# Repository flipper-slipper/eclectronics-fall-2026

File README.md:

# eclectronics-fall-2026
coursework for the eclectronics class at olin collge for the fall 2026 semester. includes pcb design, project reports, circuit simulations.

## Projects
- [Miniproject 1: USB-powered 1 Hz LED flasher PCB](miniproject-1/)

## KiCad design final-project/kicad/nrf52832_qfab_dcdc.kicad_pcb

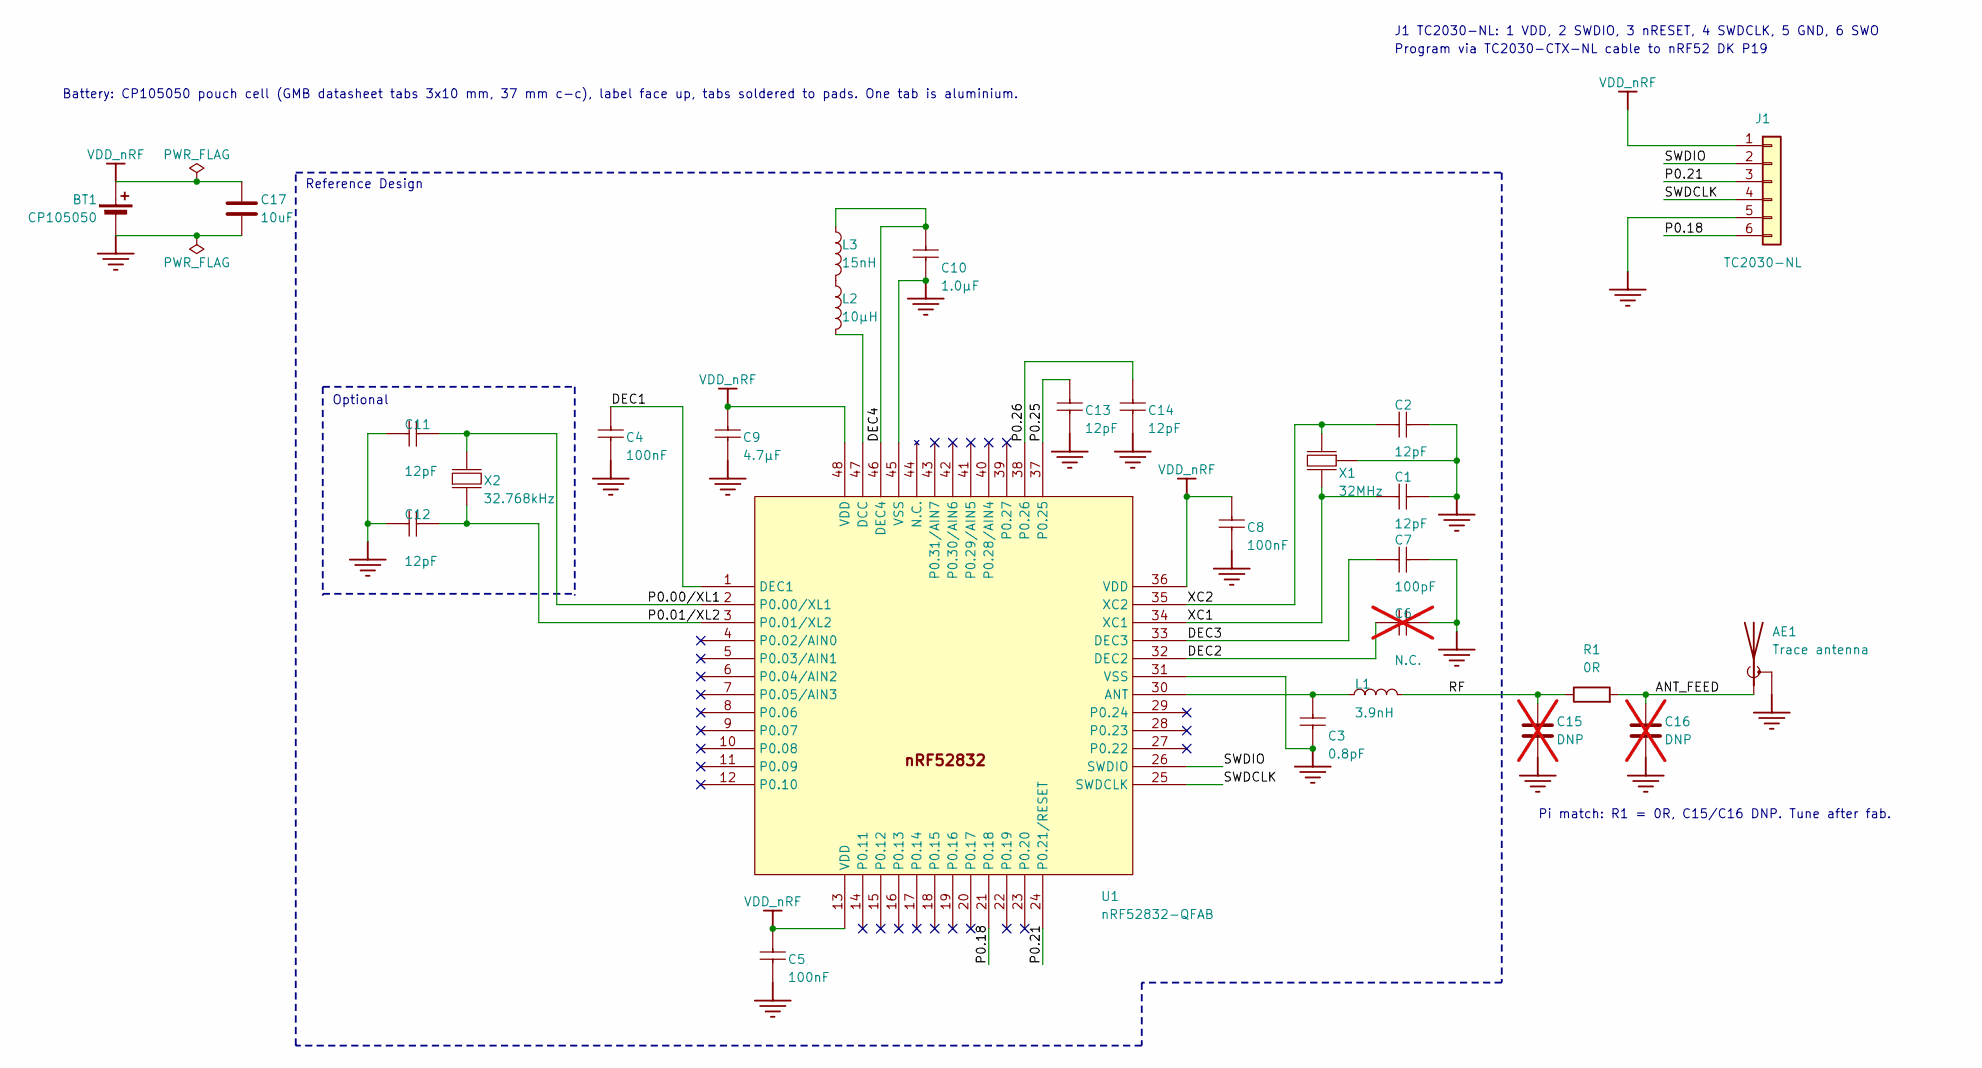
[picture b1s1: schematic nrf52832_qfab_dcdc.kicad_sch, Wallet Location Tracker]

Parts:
AE1: Trace antenna; ANT_IFA_2G4_Flex
BT1: CP105050; BAT_CP105050_Pouch_Tabs; MPN CP105050
C1, C2, C11, C12, C13, C14: 12pF; CAPC1005X04L; PART NUMBER C0402-12p
C3: 0.8pF; CAPC1005X04L; PART NUMBER C0402-0.8p
C4, C5, C8: 100nF; CAPC1005X04L; PART NUMBER C0402-100n
C6: N.C.; CAPC1005X04L; PART NUMBER C0402-N.C.; not fitted
C7: 100pF; CAPC1005X04L; PART NUMBER C0402-100p
C9: 4.7µF; CAPC1608X06L; PART NUMBER C0603-4µ7
C10: 1.0µF; CAPC1608X06L; PART NUMBER C0603-1µ0
C15, C16: DNP; C_0402_1005Metric; not fitted
C17: 10uF; C_0603_1608Metric
J1: TC2030-NL; Tag-Connect_TC2030-IDC-NL_2x03_P1.27mm_Vertical
L1: 3.9nH; INDC1005X04L; PART NUMBER L0402-3n9
L2: 10µH; INDC1608X06L; PART NUMBER L0603-10µ
L3: 15nH; INDC1005X04L; PART NUMBER L0402-15n
R1: 0R; R_0402_1005Metric
U1: nRF52832-QFAB; QFN40P600X600X90-48N; PART NUMBER nRF52832-QFAB
X1: 32MHz; BT-XTAL_2016; PART NUMBER XTAL_SMD2016_32MHz_8pF_General
X2: 32.768kHz; XTAL_3215; PART NUMBER XTAL_SMD3215_32.768kHz_9pF_General

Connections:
/ANT_FEED: AE1.1 (A), C16.1, R1.2
/DEC1: C4.1, U1.1 (DEC1)
/DEC2: C6.2, U1.32 (DEC2)
/DEC3: C7.1, U1.33 (DEC3)
/DEC4: C10.2, L3.1, U1.46 (DEC4)
/P0.00/XL1: C11.1, U1.2 (P0.00/XL1), X2.1 (inp)
/P0.01/XL2: C12.1, U1.3 (P0.01/XL2), X2.2 (out)
/P0.18: J1.6, U1.21 (P0.18)
/P0.21: J1.3, U1.24 (P0.21/RESET)
/P0.25: C13.1, U1.37 (P0.25)
/P0.26: C14.1, U1.38 (P0.26)
/RF: C15.1, L1.2, R1.1
/SWDCLK: J1.4, U1.25 (SWDCLK)
/SWDIO: J1.2, U1.26 (SWDIO)
/XC1: C1.1, U1.34 (XC1), X1.1 (inp)
/XC2: C2.1, U1.35 (XC2), X1.3 (out)
GND: AE1.2 (Shield), BT1.2 (-), C1.2, C2.2, C3.1, C4.2, C5.2, C6.1, C7.2, C8.2, C9.2, C10.1, C11.2, C12.2, C13.2, C14.2, C15.2, C16.2, C17.2, J1.5, U1.31 (VSS), U1.45 (VSS), U1.49 (GND), X1.2 (GND), X1.4 (GND)
unnamed: L2.1, L3.2
unnamed: C3.2, L1.1, U1.30 (ANT)
unnamed: L2.2, U1.47 (DCC)
VDD_nRF: BT1.1 (+), C5.1, C8.1, C9.1, C17.1, J1.1, U1.13 (VDD), U1.36 (VDD), U1.48 (VDD)

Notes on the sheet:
Optional
Battery: CP105050 pouch cell (GMB datasheet tabs 3x10 mm, 37 mm c-c), label face up, tabs soldered to pads. One tab is aluminium.
Pi match: R1 = 0R, C15/C16 DNP. Tune after fab.
J1 TC2030-NL: 1 VDD, 2 SWDIO, 3 nRESET, 4 SWDCLK, 5 GND, 6 SWO
Program via TC2030-CTX-NL cable to nRF52 DK P19
Reference Design

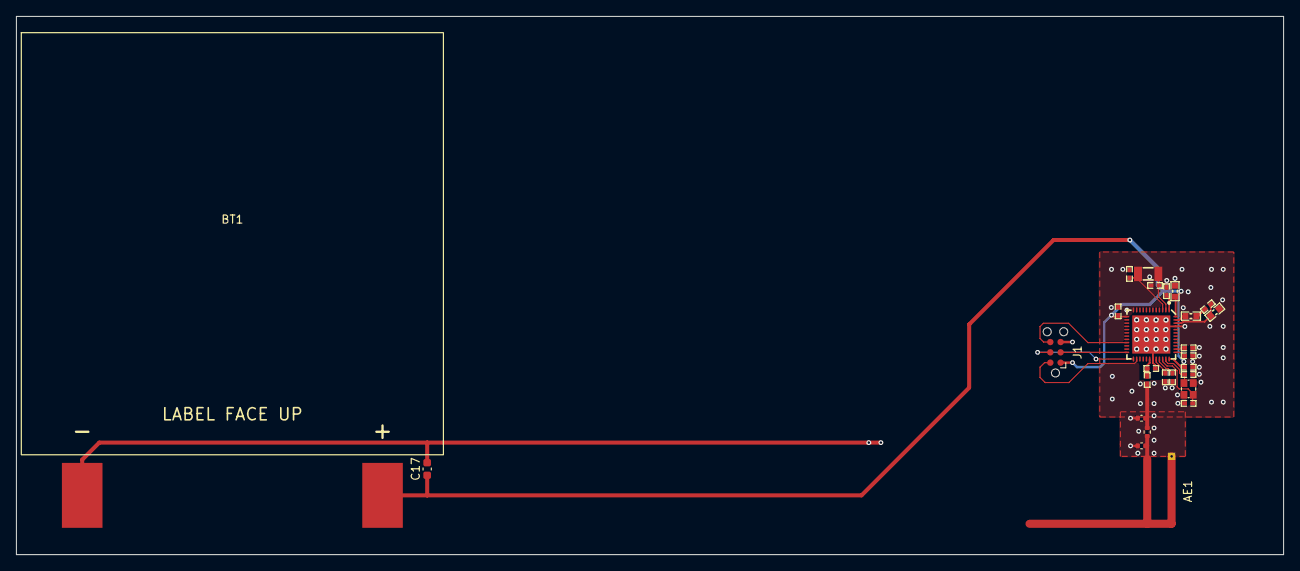
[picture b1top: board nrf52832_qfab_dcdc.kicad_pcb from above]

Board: 2 copper layers, 156.1 x 66.3 mm, 27 parts (0 on the bottom side), 21 nets.

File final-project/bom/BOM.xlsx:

Wallet Location Tracker - Bill of Materials
Ref Des | Part | Description | Manufacturer | Mfr Part # | Package | Qty / Board | Qty to Order | Unit Price ($) | Ext. Price ($) | Supplier | Supplier Part # | Link | Notes
U1 | nRF52832 | BLE 5 SoC, Arm Cortex-M4F, 256 KB flash / 32 KB RAM | Nordic Semiconductor | NRF52832-QFAB-G-R | QFN-48 6x6 mm, exposed pad | 1 | 2 | 4.87 | 9.74 | DigiKey | 4823-NRF52832-QFAB-G-RCT-ND | DigiKey | Ordering 2 = 1 spare in case QFN soldering fails. DK has QFAA (512K/64K): build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
C1, C2, C11, C12, C13, C14 | 12pF | Capacitor, NP0, ±2% | Murata | GRM1555C1H120GA01D | 0402 | 6 | 20 | 3.4000000000000002E-2 | 0.68 | DigiKey | 490-6197-1-ND | DigiKey
C3 | 0.8pF | Capacitor, NP0, ±0.1 pF | Murata | GJM1555C1HR80BB01D | 0402 | 1 | 10 | 5.8000000000000003E-2 | 0.58000000000000007 | DigiKey | 490-6080-1-ND | DigiKey
C4, C5, C8 | 100nF | Capacitor, X7R, ±10% | Murata | GRM155R71C104KA88D | 0402 | 3 | 10 | 3.5999999999999997E-2 | 0.36 | DigiKey | 490-3261-1-ND | DigiKey
C7 | 100pF | Capacitor, NP0, ±5% | Murata | GRM1555C1H101JA01D | 0402 | 1 | 10 | 2.9000000000000001E-2 | 0.29000000000000004 | DigiKey | 490-5922-1-ND | DigiKey
C9 | 4.7µF | Capacitor, X5R, ±10% | Samsung Electro-Mechanics | CL10A475KP8NNNC | 0603 | 1 | 10 | 5.8000000000000003E-2 | 0.58000000000000007 | DigiKey |  | DigiKey
C10 | 1.0µF | Capacitor, X7R, ±10% | Murata | GRT188R71C105KE13D | 0603 | 1 | 10 | 7.6999999999999999E-2 | 0.77 | DigiKey |  | DigiKey
C17 | 10µF | Capacitor, X5R, ±10%, 10 V. Bulk cap at battery | Samsung Electro-Mechanics | CL10A106KP8NNNC | 0603 | 1 | 10 | 0.19700000000000001 | 1.9700000000000002 | DigiKey |  | DigiKey
L1 | 3.9nH | High frequency chip inductor, ±0.1 nH | Murata | LQG15HS3N9B02D | 0402 | 1 | 10 | 5.2999999999999999E-2 | 0.53 | DigiKey |  | DigiKey
L2 | 10µH | Chip inductor, IDC min = 50 mA, ±20% | TDK | MLZ1608M100WT000 | 0603 | 1 | 5 | 0.1 | 0.5 | DigiKey | 445-6389-1-ND | DigiKey
L3 | 15nH | High frequency chip inductor, ±5% | Murata | LQG15HS15NJ02D | 0402 | 1 | 10 | 3.7999999999999999E-2 | 0.38 | DigiKey | 490-2625-1-ND | DigiKey
R1 | 0Ω | Antenna pi-match Z2 (series). 0 Ω jumper | YAGEO | RC0402JR-070RL | 0402 | 1 | 10 | 8.0000000000000002E-3 | 0.08 | DigiKey | 311-0.0JRCT-ND | DigiKey
X1 | 32MHz | XTAL SMD 2016, 32 MHz, CL = 8 pF, ±10 ppm tol, ±20 ppm stability | Abracon | ABM11W-32.0000MHZ-8-D1X-T3 | 2016 (2.0 x 1.6 mm) | 1 | 3 | 0.77 | 2.31 | DigiKey |  | DigiKey
X2 | 32.768kHz | XTAL SMD 3215, 32.768 kHz, CL = 9 pF, total tol ±50 ppm | Abracon | ABS07-32.768KHZ-9-T | 3215 (3.2 x 1.5 mm) | 1 | 3 | 0.85 | 2.5499999999999998 | DigiKey | 535-9544-1-ND | DigiKey
BT1 | Thin Li-MnO2 pouch cell | 3.0 V Li-MnO2 primary, 220 mAh. Max 50 mA continuous / 80 mA pulse | GMB (Huizhou Markyn) | CP105050 | Pouch 50 x 50 x 1.0 mm, 2 tabs on one edge | 1 | 2 | 5 | 10 | PowerStream | CP105050 | PowerStream | Ask supplier for pre-welded solderable (nickel) tabs. One stock tab is aluminiu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
J1 | Tag-Connect TC2030-NL footprint | SWD pads for Tag-Connect cable. Footprint only | Tag-Connect |  | 6 pads + 3 non-plated locating holes | 0 |  |  | 0
C6, C15, C16 | DNP | Not fitted. C15/C16 = antenna pi-match shunts |  |  | 0402 | 0 |  |  | 0
 |  |  |  |  |  |  |  | Parts subtotal | 31.319999999999997
Board (JLCPCB)
PCB | Flex PCB, transparent | JLCPCB flex, 2 layers, transparent PET substrate, 0.24 mm total, 1 oz ED copper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 | JLCPCB |  | 156.1 x 66.3 mm |  | 1 | 50.68 | 50.68 | JLCPCB |  | JLCPCB | Stiffener Gerber named fr4b_0.2 (bottom, FR4 0.2 mm). Stiffener holes at J1. Ma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
(stencil) | SMT stencil, top | Frameless steel stencil, top side only, custom 200 x 110 mm, ordered with the P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 | JLCPCB |  | 200 x 110 mm |  | 1 | 7.22 | 7.22 | JLCPCB |  | JLCPCB
 |  |  |  |  |  |  |  | Board subtotal | 57.9
Equipment (tools and materials, not on the board)
(tool) | Tag-Connect SWD/JTAG cable | TC2030-CTX-NL: 6-pin no-legs cable to 10-pin 0.05" Cortex debug connector | Tag-Connect | TC2030-CTX-NL | Cable |  | 1 | 42.95 | 42.95 | Tag-Connect | TC2030-CTX-NL | Tag-Connect | Normal orientation, not LEMTA. Check lab first
(material) | Low-temp solder paste | No-clean paste, Sn42/Bi57.6/Ag0.4, melts 138 °C, T4, 15 g syringe. Reflow peak 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 | Chip Quik | TS391LT | 5 cc syringe |  | 1 | 16.95 | 16.95 | DigiKey |  | DigiKey | Required: board max 200 °C
 |  |  |  |  |  |  |  | Equipment subtotal | 59.900000000000006
Shipping (shared, split between the people ordering together)
(shipping) | DigiKey shipping | FedEx/UPS Ground, flat rate per order |  |  |  |  | 1 | 6.99 | 6.99 | DigiKey |  | DigiKey
(shipping) | PowerStream shipping | Battery shipping (lithium cells go UPS/FedEx ground) |  |  |  |  | 1 | 12 | 12 | PowerStream |  |  | Estimate
(shipping) | JLCPCB shipping | UPS Express Saver, DDP (duties paid), 2-4 business days |  |  |  |  | 1 | 25.99 | 25.99 | JLCPCB
 |  |  |  |  |  |  |  | Shipping total | 44.980000000000004
 |  |  |  |  |  |  |  | Split between | 7 | people
 |  |  |  |  |  |  |  | Shipping, your share | 6.4257142857142862
 |  |  |  |  |  |  |  | Parts | 31.319999999999997
 |  |  |  |  |  |  |  | Board | 57.9
 |  |  |  |  |  |  |  | Equipment | 59.900000000000006
 |  |  |  |  |  |  |  | Shipping (your share) | 6.4257142857142862
 |  |  |  |  |  |  |  | Grand total | 155.5457142857143
 |  |  |  |  |  |  |  | Budget | 150
 |  |  |  |  |  |  |  | Remaining | -5.5457142857142969

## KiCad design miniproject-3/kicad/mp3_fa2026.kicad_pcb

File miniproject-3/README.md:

# Miniproject 3: RP2350 microcontroller dev board

KiCad project is in `kicad/` (open `mp3_fa2026.kicad_pro`). Assignment handout, BoM and reference schematic are in `docs/assignment/`.

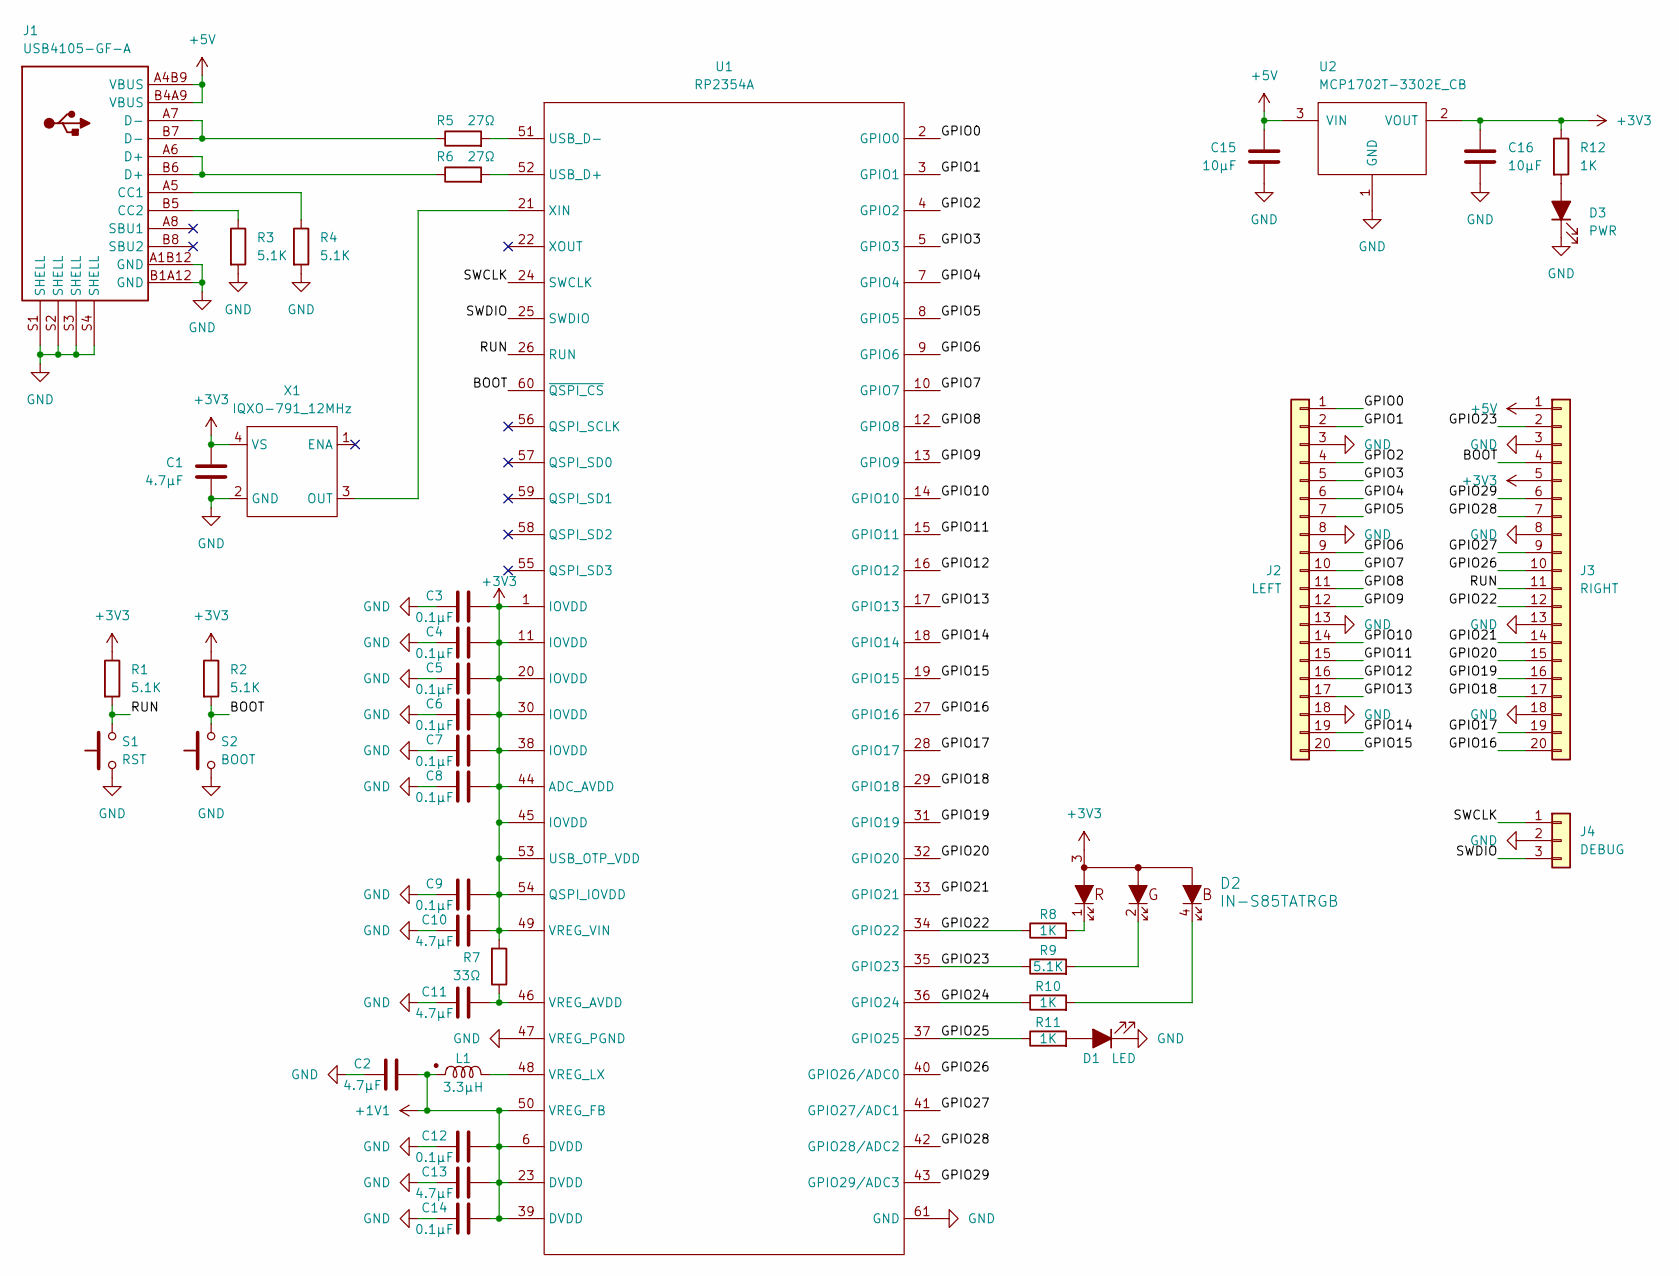
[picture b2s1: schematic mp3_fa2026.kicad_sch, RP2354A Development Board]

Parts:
C1, C2, C10: 4.7µF; C_0603_1608Metric
C3, C4, C5, C6, C7, C8, C9, C12, C14: 0.1µF; C_0402_1005Metric
C11, C13: 4.7µF; C_0402_1005Metric
C15, C16: 10µF; C_0603_1608Metric
D1: LED; LED_SunLED_XZCM2MOK54WA-1VF_0805
D2: IN-S85TATRGB; LED_Inolux_IN-S85TATRGB_2.0x1.25mm
D3: PWR; LED_LiteOn_LTST-C170_0805
J1: USB4105-GF-A; USB_C_Receptacle_GCT_USB4105-GF-A
J2: LEFT; PinHeader_1x20_P2.54mm_Vertical
J3: RIGHT; PinHeader_1x20_P2.54mm_Vertical
J4: DEBUG; PinHeader_1x03_P2.54mm_Vertical
L1: 3.3µH; L_Abracon_AOTA-B201610_2.0x1.6mm
R1, R2, R3, R4: 5.1K; R_0603_1608Metric
R5, R6: 27Ω; R_0603_1608Metric
R7: 33Ω; R_0402_1005Metric
R8, R10, R11: 1K; R_0402_1005Metric
R9: 5.1K; R_0402_1005Metric
R12: 1K; R_0603_1608Metric
S1: RST; SW_Omron_B3U-1000P
S2: BOOT; SW_Omron_B3U-1000P
U1: RP2354A; QFN-60-1EP_7x7mm_P0.4mm_EP3.4x3.4mm_RP2350A
U2: MCP1702T-3302E_CB; SOT-23_Microchip_CB
X1: IQXO-791_12MHz; Oscillator_Wurth_831056289_2.5x2.0mm

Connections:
+1V1: C2.2, C12.2, C13.2, C14.2, L1.1, U1.6 (DVDD), U1.23 (DVDD), U1.39 (DVDD), U1.50 (VREG_FB)
+3V3: C1.2, C3.2, C4.2, C5.2, C6.2, C7.2, C8.2, C9.2, C10.2, C16.1, D2.3, J3.5, R1.1, R2.1, R7.2, R12.1, U1.1 (IOVDD), U1.11 (IOVDD), U1.20 (IOVDD), U1.30 (IOVDD), U1.38 (IOVDD), U1.44 (ADC_AVDD), U1.45 (IOVDD), U1.49 (VREG_VIN), U1.53 (USB_OTP_VDD), U1.54 (QSPI_IOVDD), U2.2 (VOUT), X1.4 (VS)
+5V: C15.2, J1.A4B9 (VBUS), J1.B4A9 (VBUS), J3.1, U2.3 (VIN)
/BOOT: J3.4, R2.2, S2.2, U1.60 (~QSPI_CS)
/GPIO0: J2.1, U1.2 (GPIO0)
/GPIO1: J2.2, U1.3 (GPIO1)
/GPIO2: J2.4, U1.4 (GPIO2)
/GPIO3: J2.5, U1.5 (GPIO3)
/GPIO4: J2.6, U1.7 (GPIO4)
/GPIO5: J2.7, U1.8 (GPIO5)
/GPIO6: J2.9, U1.9 (GPIO6)
/GPIO7: J2.10, U1.10 (GPIO7)
/GPIO8: J2.11, U1.12 (GPIO8)
/GPIO9: J2.12, U1.13 (GPIO9)
/GPIO10: J2.14, U1.14 (GPIO10)
/GPIO11: J2.15, U1.15 (GPIO11)
/GPIO12: J2.16, U1.16 (GPIO12)
/GPIO13: J2.17, U1.17 (GPIO13)
/GPIO14: J2.19, U1.18 (GPIO14)
/GPIO15: J2.20, U1.19 (GPIO15)
/GPIO16: J3.20, U1.27 (GPIO16)
/GPIO17: J3.19, U1.28 (GPIO17)
/GPIO18: J3.17, U1.29 (GPIO18)
/GPIO19: J3.16, U1.31 (GPIO19)
/GPIO20: J3.15, U1.32 (GPIO20)
/GPIO21: J3.14, U1.33 (GPIO21)
/GPIO22: J3.12, R8.1, U1.34 (GPIO22)
/GPIO23: J3.2, R9.1, U1.35 (GPIO23)
/GPIO24: R10.1, U1.36 (GPIO24)
/GPIO25: R11.1, U1.37 (GPIO25)
/GPIO26: J3.10, U1.40 (GPIO26/ADC0)
/GPIO27: J3.9, U1.41 (GPIO27/ADC1)
/GPIO28: J3.7, U1.42 (GPIO28/ADC2)
/GPIO29: J3.6, U1.43 (GPIO29/ADC3)
/RUN: J3.11, R1.2, S1.2, U1.26 (RUN)
/SWCLK: J4.1, U1.24 (SWCLK)
/SWDIO: J4.3, U1.25 (SWDIO)
GND: C1.1, C2.1, C3.1, C4.1, C5.1, C6.1, C7.1, C8.1, C9.1, C10.1, C11.1, C12.1, C13.1, C14.1, C15.1, C16.2, D1.1 (K), D3.1 (K), J1.A1B12 (GND), J1.B1A12 (GND), J1.S1 (SHELL_S1), J1.S2 (SHELL_S1), J1.S3 (SHELL_S1), J1.S4 (SHELL_S1), J2.3, J2.8, J2.13, J2.18, J3.3, J3.8, J3.13, J3.18, J4.2, R3.2, R4.2, S1.1, S2.1, U1.47 (VREG_PGND), U1.61 (GND), U2.1 (GND), X1.2 (GND)
unnamed: D1.2 (A), R11.2
unnamed: D2.1, R8.2
unnamed: D2.2, R9.2
unnamed: D2.4, R10.2
unnamed: D3.2 (A), R12.2
unnamed: J1.A5 (CC1_A5), R4.1
unnamed: J1.B5 (CC2_B5), R3.1
unnamed: J1.A6 (D+_A6), J1.B6 (D+_B6), R6.1
unnamed: J1.A7 (D-_A7), J1.B7 (D-_B7), R5.1
unnamed: R6.2, U1.52 (USB_D+)
unnamed: R5.2, U1.51 (USB_D-)
unnamed: C11.2, R7.1, U1.46 (VREG_AVDD)
unnamed: L1.2, U1.48 (VREG_LX)
unnamed: U1.21 (XIN), X1.3 (OUT)

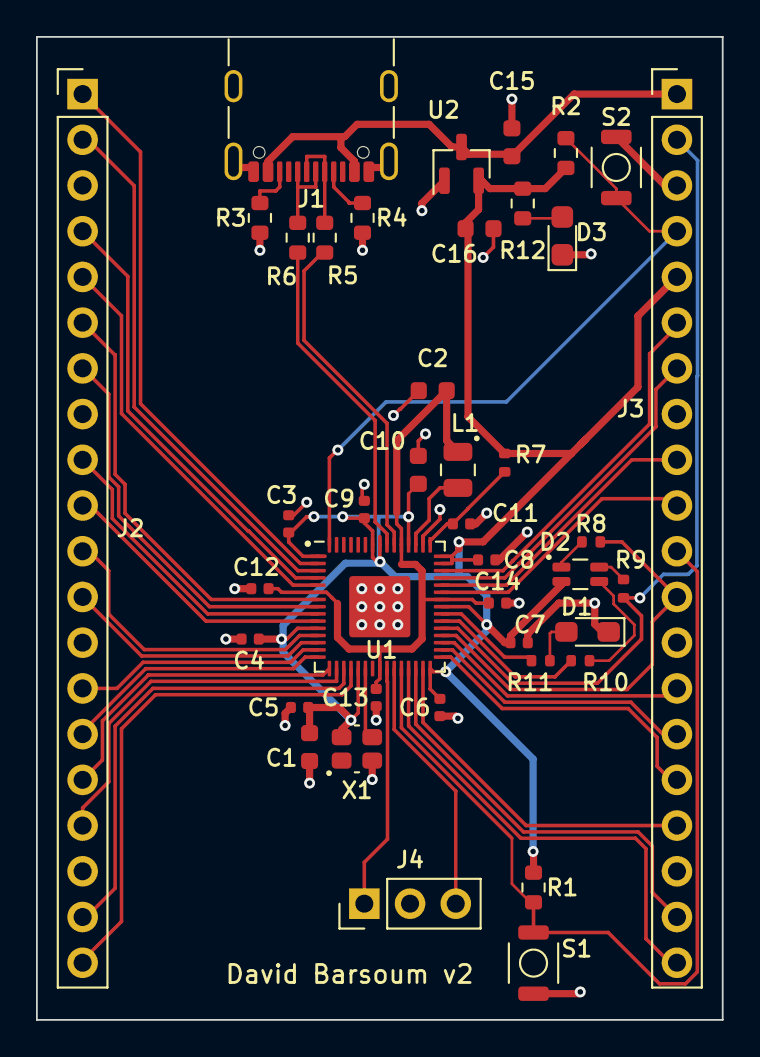
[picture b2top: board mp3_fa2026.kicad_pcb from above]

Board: 2 copper layers, 38.1 x 54.6 mm, 41 parts (0 on the bottom side), 52 nets.

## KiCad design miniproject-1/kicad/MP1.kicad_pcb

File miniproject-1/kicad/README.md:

# MP1 LED Flasher — KiCad project

Open **MP1.kicad_pro** in KiCad 10. The schematic and completed board share this name. Keep the two library tables, MP1_Analog.kicad_sym, and MP1_Footprints.pretty alongside them.

## Minimal schematic

The schematic is one integrated drawing with a shared 3.3 V supply rail and the triangular op-amp symbol. Component values, pin connections, footprints and PCB associations are unchanged. Timing calculations and assembly details remain in MP1-Notes.md. The page retains your name and title block.

KiCad ERC: **0 errors and 0 warnings**. All 10 nets and 15 component associations match the completed PCB. See checks/minimal-layout-verification.json for the schematic simplification, and PCB-verification.json for the current board.

## Completed PCB

- Plain 18 × 22 mm rectangular outline (396 mm²), square corners, and 1.6 mm board thickness.
- Decorative titles, dates, size labels and nonessential board text removed. Component references, footprint outlines and polarity marks retained; no bottom-side printed text. References are aligned beside their components, with clearance from pads and outlines.
- Two copper layers. All 15 component bodies mount on top. All power and signal traces are routed on the top layer. The bottom ground plane has no routed tracks; the USB through-hole pads still appear on both copper layers.
- 0.25 mm signal tracks with a short 0.18 mm output escape beneath U1, and 0.4 mm main power routes; 0.20 mm minimum copper clearance; 0.30 mm copper-to-edge clearance.
- 9 ground through vias: 0.70 mm copper diameter and 0.35 mm drill. No via drills intersect component pads; minimum checked separation from a pad bounding box is 0.10 mm.
- C5 power pad is 1.788 mm from U1 pin 5, joined by a short direct trace. The high-impedance timing components sit beside U1.
- The USB plug projects beyond the bottom edge. The LED sits at the opposite end.

## Checks

KiCad 10.0.6 GUI DRC, with ground copper refilled: **0 errors, 0 warnings, 0 unconnected pads**. No individual DRC exclusions were added. The report lists five standard ignored check categories.

An independent comparison verified all 15 footprint values, footprint names and schematic UUID associations, and every pin on all 10 schematic nets. KiCad's Schematic Parity tab was not run in the standalone editor; the independent comparison is recorded in PCB-verification.json. The simplified schematic passed ERC with zero errors and warnings.

This design has not been fabricated or electrically tested. Measure the assembled oscillator period and check the 3.3 V rail during first power-up. Timing tolerance assumptions are documented in MP1-Notes.md.

## Included files

- Editable KiCad project, schematic, PCB, and project-specific libraries.
- ../docs/Schematic.pdf and the approved-parts BOM.
- Component-positions.csv (all top components, including the manually assembled USB plug).
- DRC.rpt and PCB-verification.json.
- previews/board-top.png: KiCad 3D render. The USB connector body is omitted because its custom footprint has no 3D model; its actual plated pads, slots and locating holes are present.
- previews/top-layout.svg and bottom-copper.svg: KiCad layer plots.
- fabrication/: top/bottom copper, solder mask and silkscreen Gerbers, board outline, separate plated/nonplated drill files, and drill maps/report. All share the same absolute origin; dimensions are millimetres. The plated shell slots use routed Excellon slots.

## Before ordering

Check the supplied Molex 0480370001 connector against a 1:1 print, including pin numbering, shell slots and board-edge position. It is a through-hole connector from the approved parts list; confirm it is the intended exception to the assignment's general surface-mount wording. All other parts are surface-mount. Use the supplied MPNs and inspect LED polarity during assembly. No order has been placed.

## Review of flagged issues

Review-of-Flagged-Issues.md records the earlier USB-edge, U1 clearance and silkscreen review. The current board has a rectangular outline, no decorative text, all routing on F.Cu, and aligned component references. Moving +3V3 and OUT to the top removed six vias in total. U1's remaining ground via moved 0.3 mm to clear the output escape. Component locations and circuit connections are unchanged. The board has 56 track segments and 9 ground vias. See checks/top-routing-verification.json for the current routing and label checks. The preview images and manufacturing files show the current board.

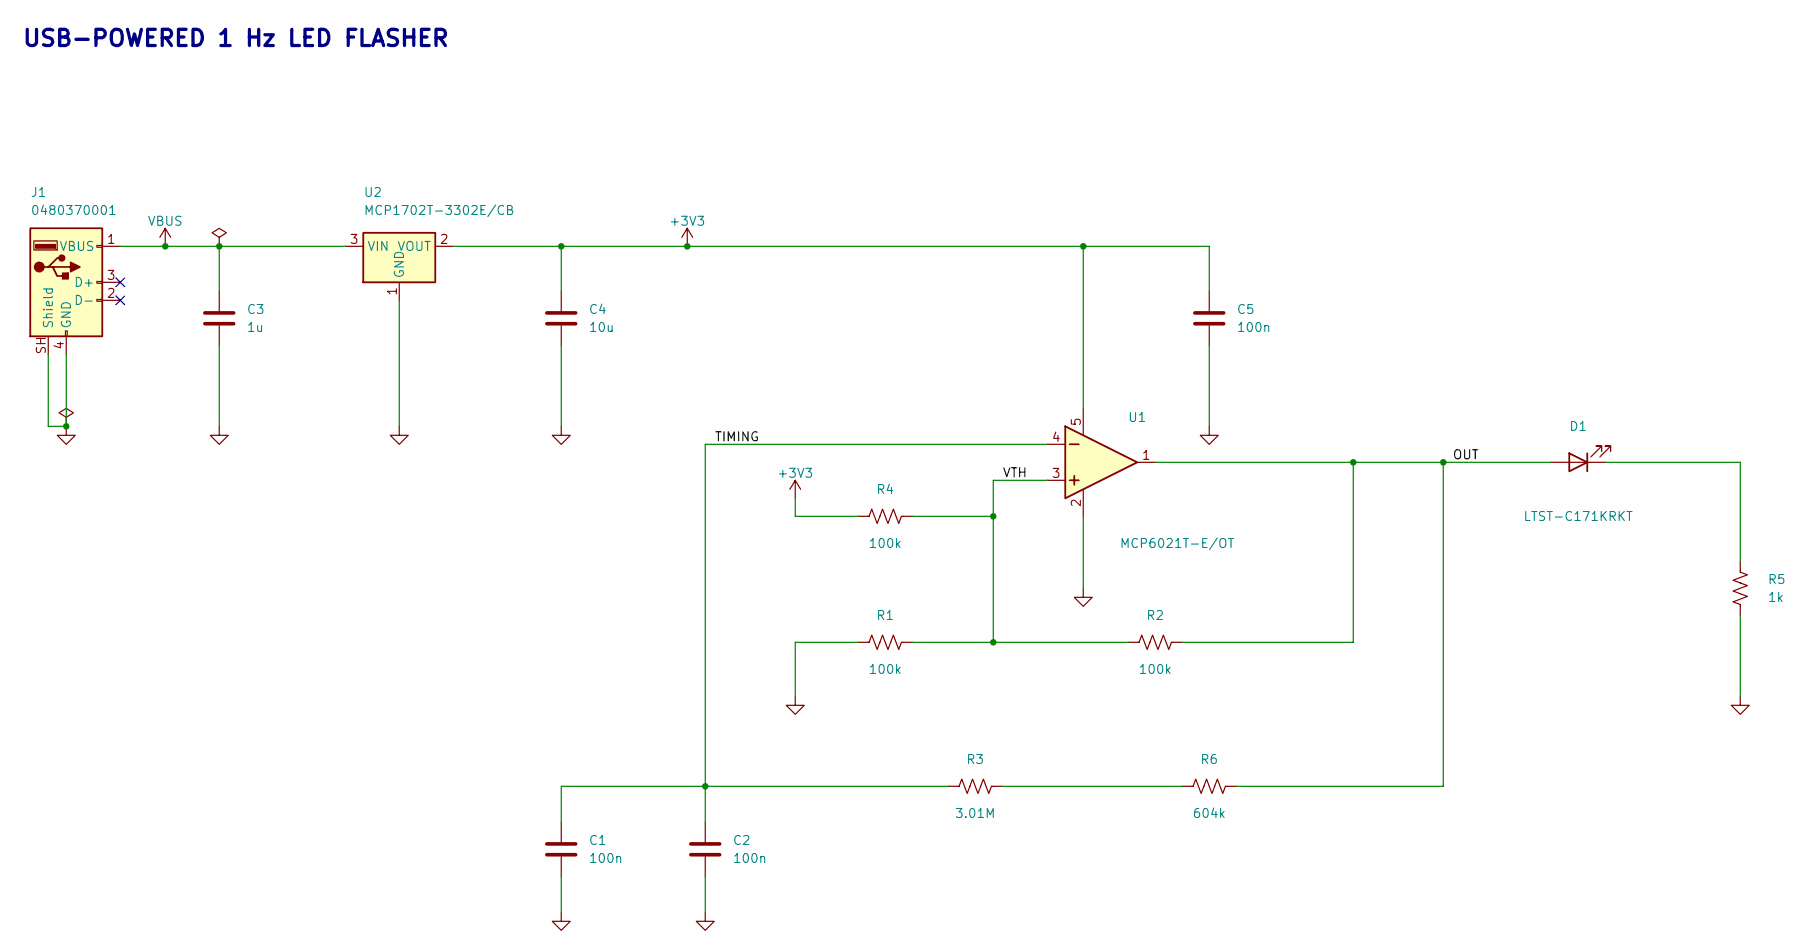
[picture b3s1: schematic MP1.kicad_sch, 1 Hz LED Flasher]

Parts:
C1, C2, C5: 100n; C_0603_1608Metric; Voltage 50 V; Tolerance 5%; MPN CC0603JRX7R9BB104; DigiKey 311-1779-1-ND
C3: 1u; C_0603_1608Metric; Voltage 25 V; Tolerance 10%; MPN C0603C105K3RACTU; DigiKey 399-7376-1-ND
C4: 10u; C_0603_1608Metric; Voltage 16 V; Tolerance 10%; MPN GRT188R61C106KE13D; DigiKey 490-12317-1-ND
D1: LTST-C171KRKT; LED_0805_2012Metric; MPN LTST-C171KRKT; DigiKey 160-1427-1-ND
J1: 0480370001; USB_A_Molex_48037-0001_Horizontal; MPN 0480370001; DigiKey WM17117-ND
R1, R2, R4: 100k; R_0603_1608Metric; Tolerance 1%; MPN RC0603FR-07100KL; DigiKey 311-100KHRCT-ND
R3: 3.01M; R_0603_1608Metric; Tolerance 1%; MPN RC0603FR-073M01L; DigiKey 311-3.01MHRCT-ND
R5: 1k; R_0603_1608Metric; Tolerance 1%; MPN RC0603FR-071KL; DigiKey 311-1.00KHRCT-ND
R6: 604k; R_0603_1608Metric; Tolerance 1%; MPN RC0603FR-07604KL; DigiKey 311-604KHRCT-ND
U1: MCP6021T-E/OT; SOT-23-5; MPN MCP6021T-E/OT; DigiKey MCP6021T-E/OTCT-ND
U2: MCP1702T-3302E/CB; SOT-23; MPN MCP1702T-3302E/CB; DigiKey MCP1702T-3302E/CBCT-ND

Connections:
+3V3: C4.1, C5.1, R4.1, U1.5 (VDD), U2.2 (VOUT)
/OUT: D1.2 (A), R2.2, R6.2, U1.1
/TIMING: C1.1, C2.1, R3.1, U1.4 (-)
/VTH: R1.2, R2.1, R4.2, U1.3 (+)
GND: C1.2, C2.2, C3.2, C4.2, C5.2, J1.4 (GND), J1.SH (Shield), R1.1, R5.2, U1.2 (VSS), U2.1 (GND)
unnamed: D1.1 (K), R5.1
unnamed: R3.2, R6.1
VBUS: C3.1, J1.1 (VBUS), U2.3 (VIN)

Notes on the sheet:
USB-POWERED 1 Hz LED FLASHER

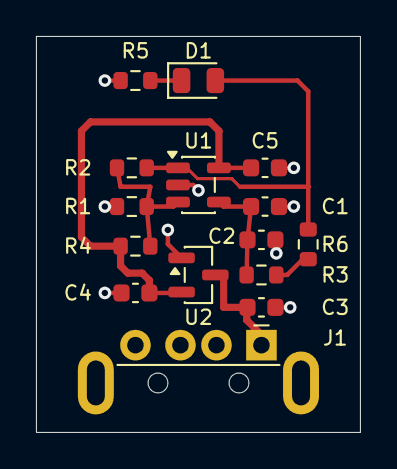
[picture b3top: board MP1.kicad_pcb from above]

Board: 2 copper layers, 18.0 x 22.0 mm, 15 parts (0 on the bottom side), 8 nets.
